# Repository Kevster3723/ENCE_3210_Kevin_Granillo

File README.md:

# ENCE_3210_Kevin_Granillo

Hello World
Kevin

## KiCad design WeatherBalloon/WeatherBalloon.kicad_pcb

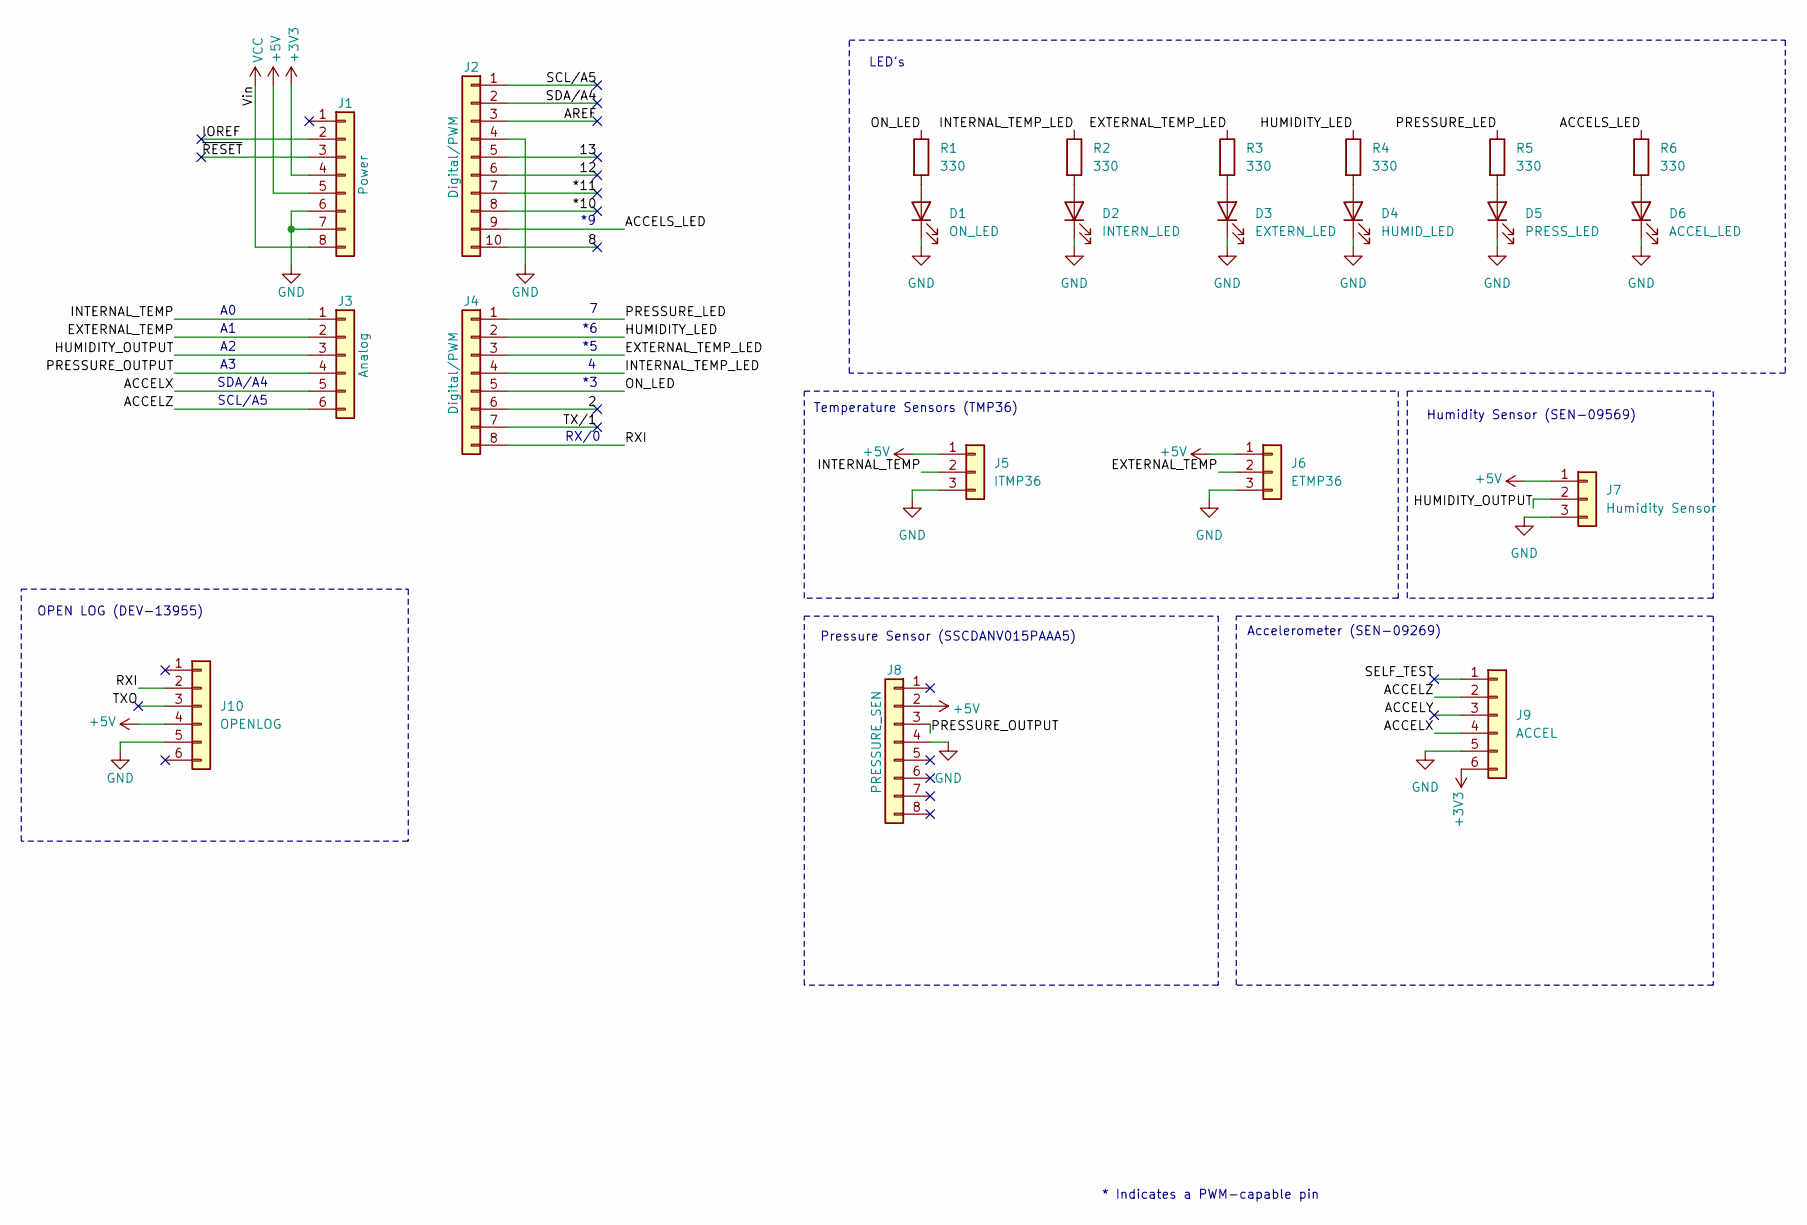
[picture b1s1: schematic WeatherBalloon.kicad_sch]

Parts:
D1: ON_LED; LED_D5.0mm
D2: INTERN_LED; LED_D5.0mm
D3: EXTERN_LED; LED_D5.0mm
D4: HUMID_LED; LED_D5.0mm
D5: PRESS_LED; LED_D5.0mm
D6: ACCEL_LED; LED_D5.0mm
J1: Power; PinSocket_1x08_P2.54mm_Vertical
J2: Digital/PWM; PinSocket_1x10_P2.54mm_Vertical
J3: Analog; PinSocket_1x06_P2.54mm_Vertical
J4: Digital/PWM; PinSocket_1x08_P2.54mm_Vertical
J5: ITMP36; TMP36
J6: ETMP36; TMP36
J7: Humidity Sensor; PinHeader_1x03_P2.54mm_Vertical
J8: PRESSURE_SEN; DIP-8_W7.62mm
J9: ACCEL; PinHeader_1x06_P2.54mm_Vertical
J10: OPENLOG; PinHeader_1x06_P2.00mm_Vertical
R1, R2, R3, R4, R5, R6: 330; R_Axial_DIN0207_L6.3mm_D2.5mm_P10.16mm_Horizontal

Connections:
+3V3: J1.4, J9.6
+5V: J1.5, J5.1, J6.1, J7.1, J8.2, J10.4
/2: J4.6
/8: J2.10
/12: J2.6
/13: J2.5
/*10: J2.8
/*11: J2.7
/ACCELS_LED: J2.9, R6.1
/ACCELX: J3.5, J9.4
/ACCELY: J9.3
/ACCELZ: J3.6, J9.2
/AREF: J2.3
/EXTERNAL_TEMP: J3.2, J6.2
/EXTERNAL_TEMP_LED: J4.3, R3.1
/HUMIDITY_LED: J4.2, R4.1
/HUMIDITY_OUTPUT: J3.3, J7.2
/INTERNAL_TEMP: J3.1, J5.2
/INTERNAL_TEMP_LED: J4.4, R2.1
/IOREF: J1.2
/ON_LED: J4.5, R1.1
/PRESSURE_LED: J4.1, R5.1
/PRESSURE_OUTPUT: J3.4, J8.3
/RXI: J4.8, J10.2
/SCL/A5: J2.1
/SDA/A4: J2.2
/SELF_TEST: J9.1
/TXO: J10.3
/TX/1: J4.7
/~RESET: J1.3
GND: D1.1 (K), D2.1 (K), D3.1 (K), D4.1 (K), D5.1 (K), D6.1 (K), J1.6, J1.7, J2.4, J5.3, J6.3, J7.3, J8.4, J9.5, J10.5
unnamed: D1.2 (A), R1.2
unnamed: D2.2 (A), R2.2
unnamed: D3.2 (A), R3.2
unnamed: D4.2 (A), R4.2
unnamed: D5.2 (A), R5.2
unnamed: D6.2 (A), R6.2
VCC: J1.8

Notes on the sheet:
Accelerometer (SEN-09269)
OPEN LOG (DEV-13955)
SCL/A5
RX/0
Pressure Sensor (SSCDANV015PAAA5)
LED's
SDA/A4
* Indicates a PWM-capable pin
Temperature Sensors (TMP36)
Humidity Sensor (SEN-09569)

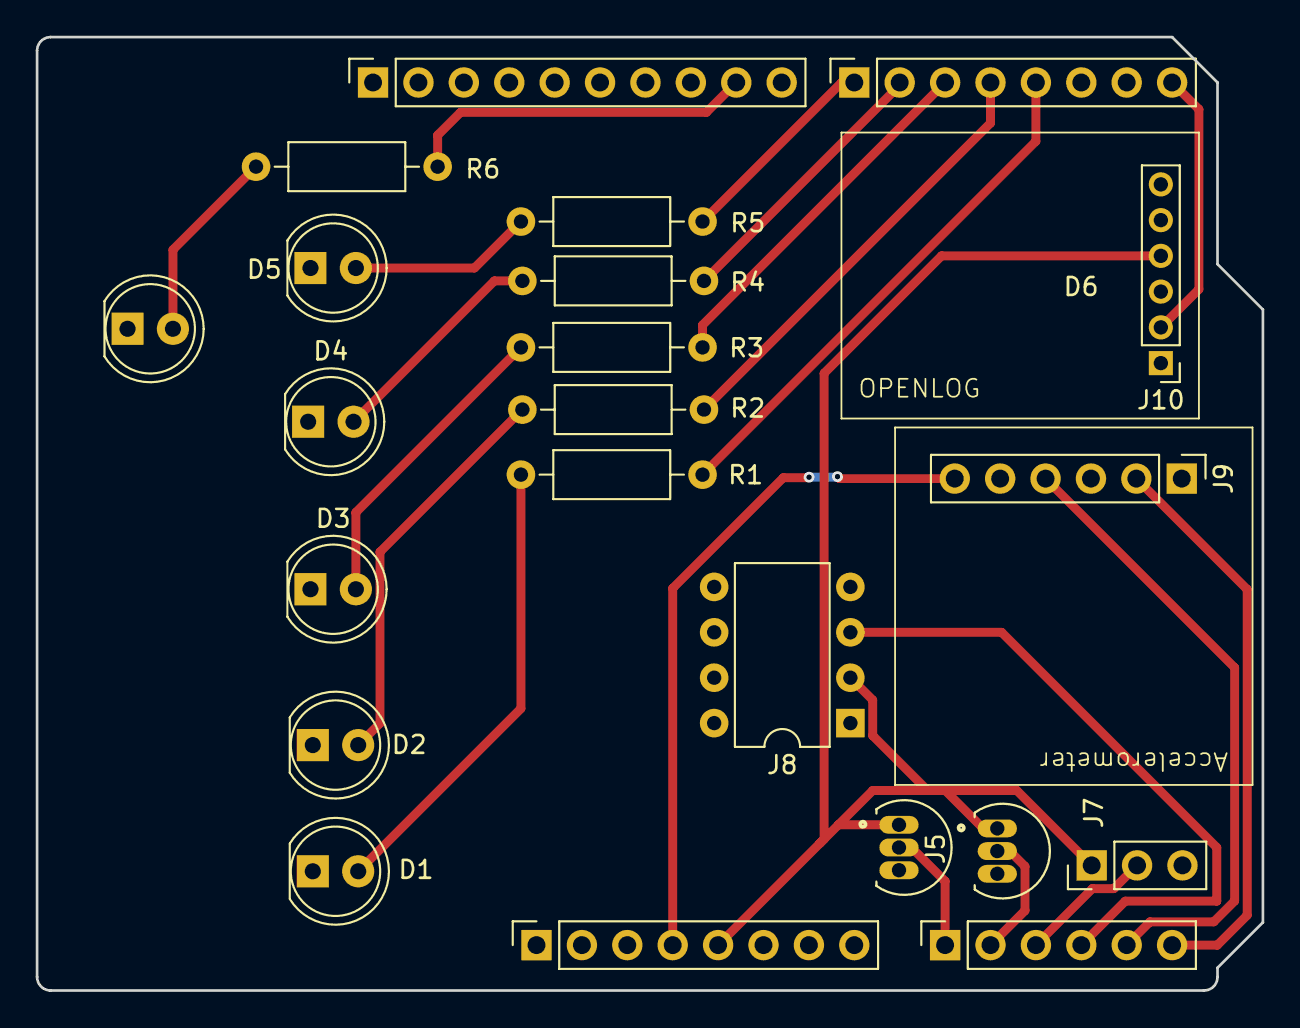
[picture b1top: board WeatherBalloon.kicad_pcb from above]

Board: 2 copper layers, 68.6 x 53.3 mm, 22 parts (0 on the bottom side), 22 nets.

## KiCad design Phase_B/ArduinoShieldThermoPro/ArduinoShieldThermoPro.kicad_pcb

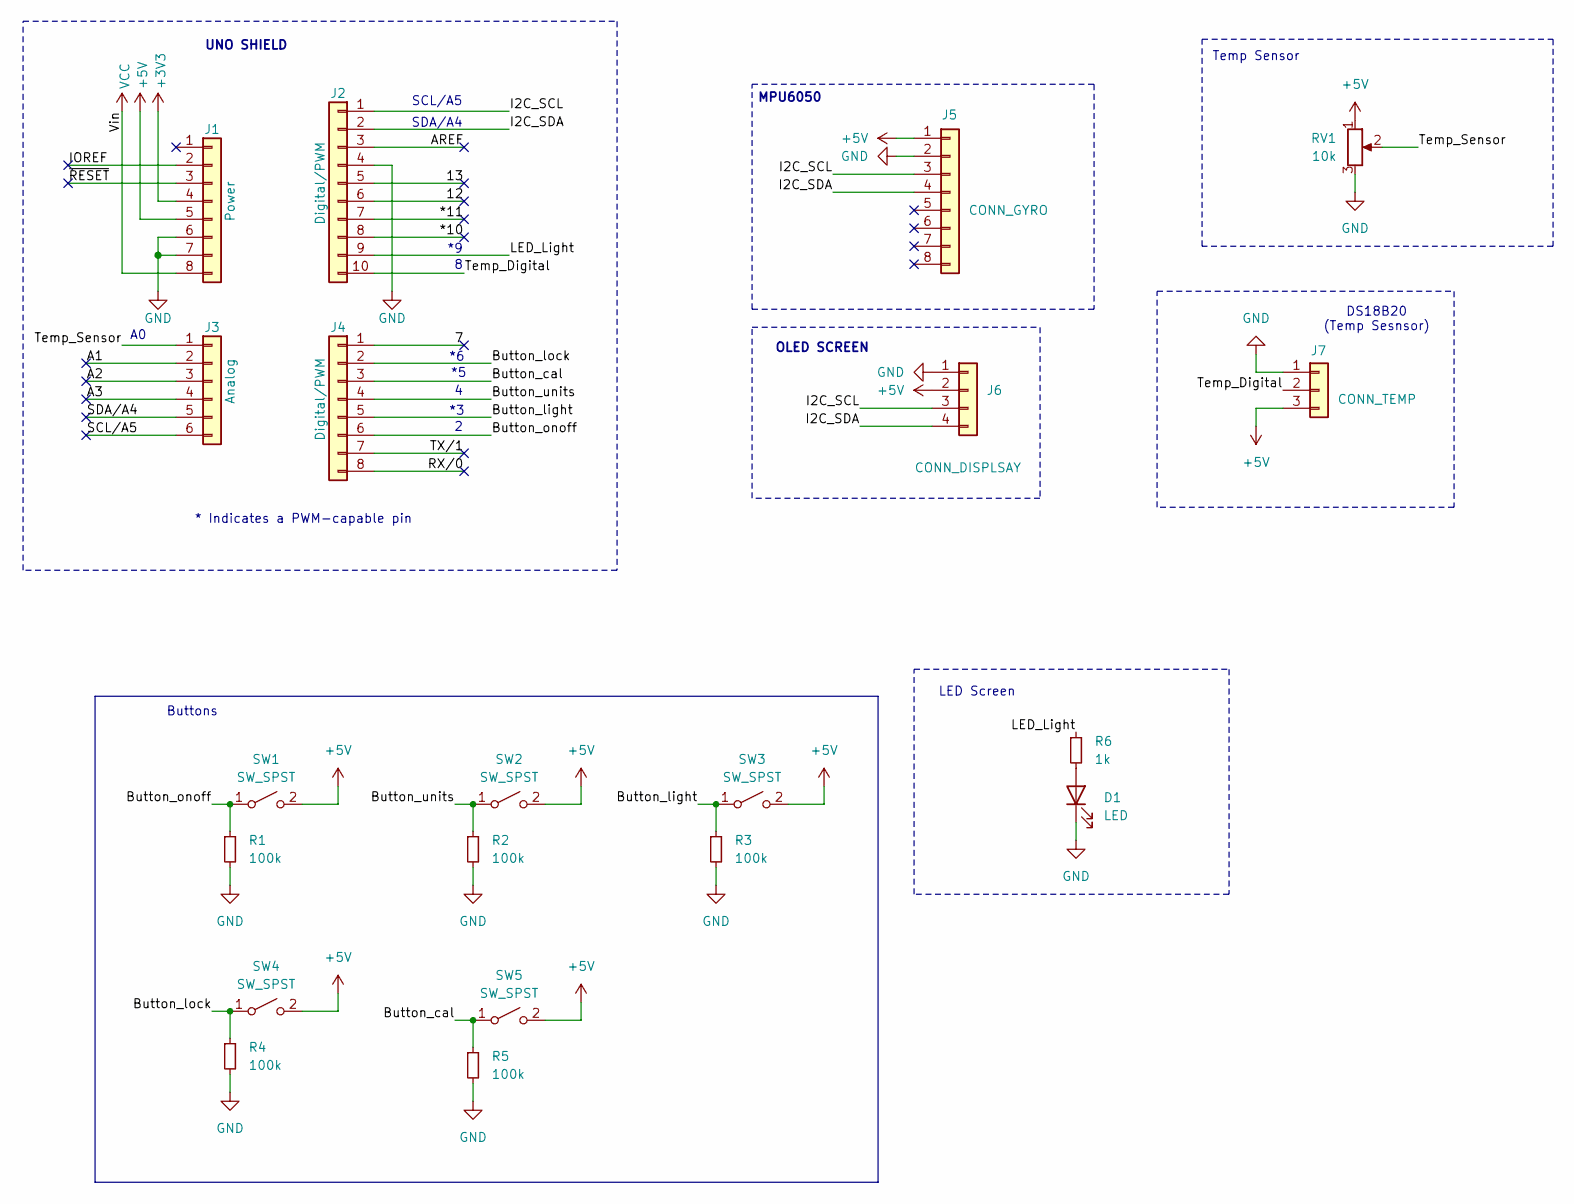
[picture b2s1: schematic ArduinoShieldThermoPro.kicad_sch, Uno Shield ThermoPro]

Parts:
D1: LED; LED_D5.0mm
J1: Power; PinSocket_1x08_P2.54mm_Vertical
J2: Digital/PWM; PinSocket_1x10_P2.54mm_Vertical
J3: Analog; PinSocket_1x06_P2.54mm_Vertical
J4: Digital/PWM; PinSocket_1x08_P2.54mm_Vertical
J5: CONN_GYRO; PinSocket_1x08_P2.54mm_Vertical
J6: CONN_DISPLSAY; PinSocket_1x04_P2.54mm_Vertical
J7: CONN_TEMP; JST_XH_B3B-XH-A_1x03_P2.50mm_Vertical
R1, R2, R3, R4, R5: 100k; R_Axial_DIN0207_L6.3mm_D2.5mm_P10.16mm_Horizontal
R6: 1k; R_Axial_DIN0207_L6.3mm_D2.5mm_P10.16mm_Horizontal
RV1: 10k; Potentiometer_Bourns_3386P_Vertical
SW1, SW2, SW3, SW4, SW5: SW_SPST; SW_PUSH_6mm

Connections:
+3V3: J1.4
+5V: J1.5, J5.1, J6.2, J7.3, RV1.1, SW1.2 (B), SW2.2 (B), SW3.2 (B), SW4.2 (B), SW5.2 (B)
/7: J4.1
/12: J2.6
/13: J2.5
/*10: J2.8
/*11: J2.7
/A1: J3.2
/A2: J3.3
/A3: J3.4
/AREF: J2.3
/Button_cal: J4.3, R5.1, SW5.1 (A)
/Button_light: J4.5, R3.1, SW3.1 (A)
/Button_lock: J4.2, R4.1, SW4.1 (A)
/Button_onoff: J4.6, R1.1, SW1.1 (A)
/Button_units: J4.4, R2.1, SW2.1 (A)
/I2C_SCL: J2.1, J5.3, J6.3
/I2C_SDA: J2.2, J5.4, J6.4
/IOREF: J1.2
/LED_Light: J2.9, R6.1
/RX/0: J4.8
/SCL/A5: J3.6
/SDA/A4: J3.5
/TX/1: J4.7
/Temp_Digital: J2.10, J7.2
/Temp_Sensor: J3.1, RV1.2
/~RESET: J1.3
GND: D1.1 (K), J1.6, J1.7, J2.4, J5.2, J6.1, J7.1, R1.2, R2.2, R3.2, R4.2, R5.2, RV1.3
unnamed: D1.2 (A), R6.2
VCC: J1.8

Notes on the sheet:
DS18B20 (Temp Sesnsor)
MPU6050
OLED SCREEN
LED Screen
Temp Sensor
Buttons
UNO SHIELD
SDA/A4
* Indicates a PWM-capable pin
SCL/A5

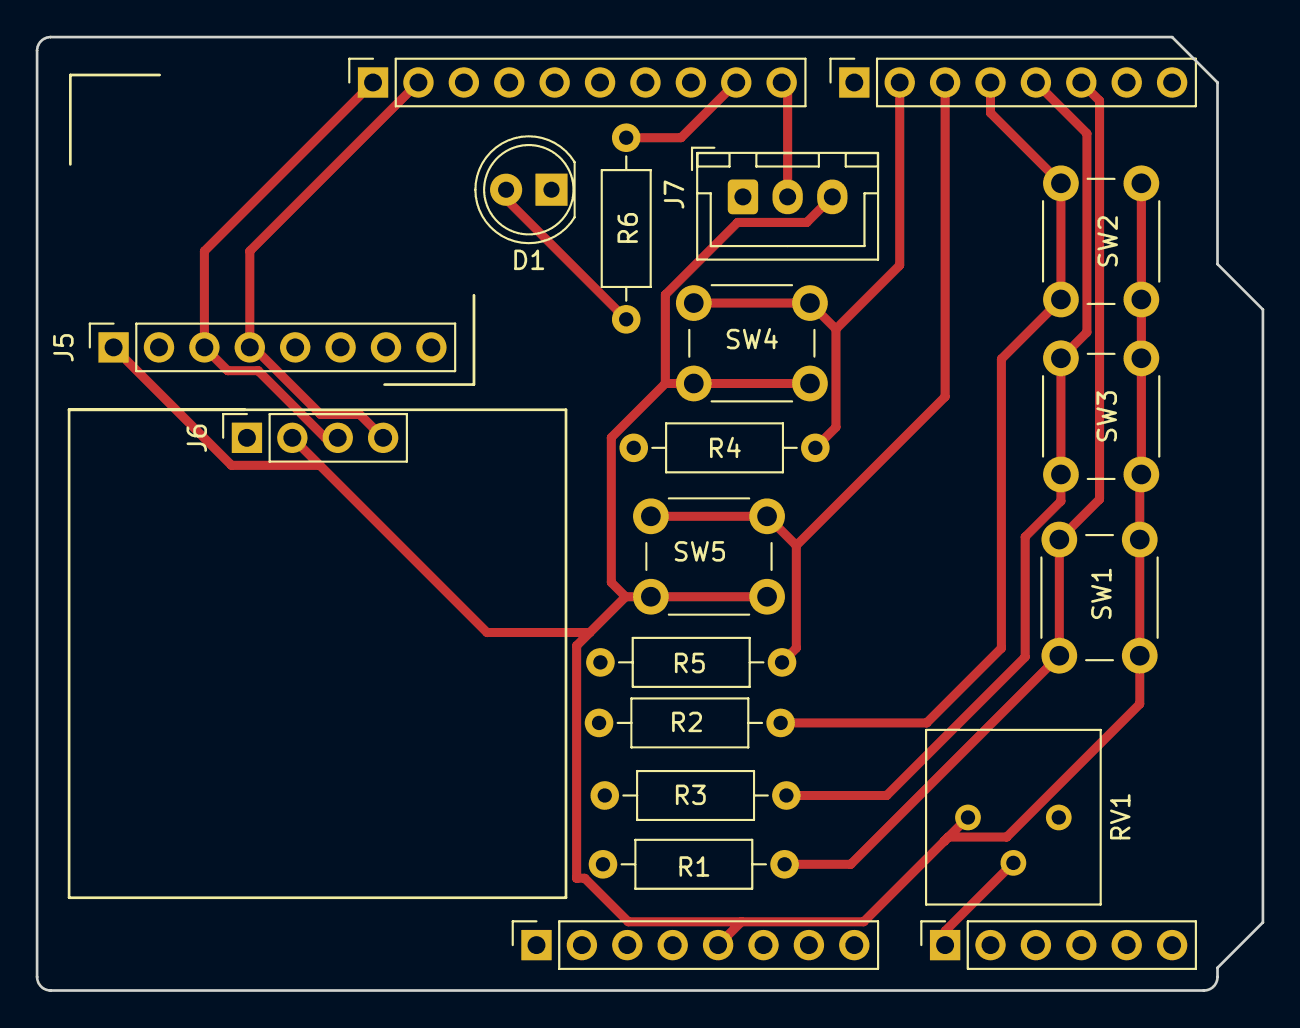
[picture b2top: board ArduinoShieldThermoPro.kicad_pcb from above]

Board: 2 copper layers, 68.6 x 53.3 mm, 20 parts (0 on the bottom side), 13 nets.

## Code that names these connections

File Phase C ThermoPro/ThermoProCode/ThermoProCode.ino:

/*
*
* Kevin Granillo
* February 26, 2025
*
* This code is made for a thermometer that uses a one wire digital temperature sensor
* The criteria for the thermometer are that it must switch between celcius and fahrenheit
* It must flip the screen orientation depending on the gyro readings
* It must have a button for the light on the back lit display
* Lastly, it must lock the reading when a button is pressed
*
* Side note, everything works well, the only issue ecnountered was with the mechanical buttons which bounce
*
*/

// Defining all buttons used
#define BUTTON_LOCK 3
#define BUTTON_CAL 5
#define BUTTON_UNITS 4
#define BUTTON_LIGHT 6
#define BUTTON_ONOFF 2

#define LED 9 // LED for backlit display

#define TEMP_DIGITAL 8 // Digital Temp Sensor
#define TEMP_ANALOG A0 // Potentiometer playing as analog Temp Sensor

#define TIMERCOMPAREVALUE1 46875 // Resets Timer 1 after 3 seconds
#define TIMERCOMPAREVALUE2 255 // Resets Timer 2 after overflow

#define ONE_WIRE_BUS 8 // Temp Sensor Pin
#define OUTPUT_READABLE_ACCELGYRO

// All included libraries for Temp sensor, gyro, and Screen
#include <SPI.h>
#include <OneWire.h>
#include <DallasTemperature.h>
#include <Adafruit_GFX.h>
#include <Adafruit_SSD1306.h>
#include <I2Cdev.h>
#include <MPU6050.h>
#include "images.h" // Images displayed on screen (LOCK, UNCLOCKED LOCK, C,F)

#define SCREEN_WIDTH 128 // OLED display width, in pixels
#define SCREEN_HEIGHT 32 // OLED display height, in pixels

#if I2CDEV_IMPLEMENTATION == I2CDEV_ARDUINO_WIRE
    #include "Wire.h"
#endif

// Declaration for an SSD1306 display connected to I2C (SDA, SCL pins)
// The pins for I2C are defined by the Wire-library. 
// On an arduino UNO:       A4(SDA), A5(SCL)
// On an arduino MEGA 2560: 20(SDA), 21(SCL)
// On an arduino LEONARDO:   2(SDA),  3(SCL), ...
#define OLED_RESET     -1 // Reset pin # (or -1 if sharing Arduino reset pin)
#define SCREEN_ADDRESS 0x3C ///< See datasheet for Address; 0x3D for 128x64, 0x3C for 128x32
Adafruit_SSD1306 display(SCREEN_WIDTH, SCREEN_HEIGHT, &Wire, OLED_RESET);

OneWire oneWire(ONE_WIRE_BUS);
DallasTemperature sensors(&oneWire);

enum State_e{OFF,ON,LOCK}; // Defines state machine (On, Off, and Locked)
enum State_e gState = OFF; // Default state is off

// Global Variables for Temp
float gTempC = 0;
float gTempF = 0;

// Global Variables used as flags
char gFlag_OnOff = 0;
char gFlag_Lock = 0;
char gFlag_Units = 0; 
char gFlag_Light = 0;
char gFlag_ReadTemp = 0;

// Variables for Gyroscope
int16_t ax, ay, az;
int16_t gx, gy, gz;
MPU6050 accelgyro;
//MPU6050 accelgyro(0x69); // <-- use for AD0 high



void setup() {
  Serial.begin(9600); // Begin Serial Comunication 

  // Buttons and Sensors are Inputs, LED is output
  pinMode(BUTTON_LOCK,INPUT);
  pinMode(BUTTON_CAL,INPUT);
  pinMode(BUTTON_UNITS,INPUT);
  pinMode(BUTTON_LIGHT,INPUT);
  pinMode(BUTTON_ONOFF,INPUT);
  pinMode(TEMP_DIGITAL,INPUT);
  pinMode(TEMP_ANALOG,INPUT);
  pinMode(LED,OUTPUT);

#if I2CDEV_IMPLEMENTATION == I2CDEV_ARDUINO_WIRE
  Wire.begin();
#elif I2CDEV_IMPLEMENTATION == I2CDEV_BUILTIN_FASTWIRE
  Fastwire::setup(400, true);
#endif

  sensors.begin();
  accelgyro.initialize();

  // SSD1306_SWITCHCAPVCC = generate display voltage from 3.3V internally
  if(!display.begin(SSD1306_SWITCHCAPVCC, SCREEN_ADDRESS)) {
    Serial.println(F("SSD1306 allocation failed"));
    for(;;); // Don't proceed, loop forever
  }
  // Show initial display buffer contents on the screen --
  // the library initializes this with an Adafruit splash screen.
  display.display();
  delay(2000); // Pause for 2 seconds
  // Clear the buffer
  display.clearDisplay();

  attachInterrupt(digitalPinToInterrupt(BUTTON_ONOFF), isr_onoff,CHANGE); // Attach interrupt to OnOff button
  attachInterrupt(digitalPinToInterrupt(BUTTON_LOCK), isr_lock, CHANGE); // Attach interrupt to Lock button

  noInterrupts(); // Disable interrupts
  TCCR1B = 0; // Timer 1
  TCCR1A = 0;

  TCCR2B = 0; // Timer 2
  TCCR2A = 0;

  TCCR2B |= (1<<WGM21); // Clock set to CTC
  TCCR2B |= (1<<CS22); //Clock 2 prescale by 1024
  TCCR2B |= (1<<CS21);
  TCCR2B |= (1<<CS20);

  OCR1A = TIMERCOMPAREVALUE1; // Reset after 3 seconds
  OCR2A = TIMERCOMPAREVALUE2; // Reset after overflow

  TIMSK1 |= (1<<OCIE1A); // Attach interrupt to timer 1
  TIMSK2 |= (1<<OCIE2A); // Attach interrupt to timer 2
  
  interrupts(); // Enable interrupts
}

void loop() {
  // put your main code here, to run repeatedly:
  display.clearDisplay(); // Clear display after each itteration 
  accelgyro.getMotion6(&ax, &ay, &az, &gx, &gy, &gz); // Read Gyro

  switch(gState){ // State Machine
  
    case OFF:
      display.clearDisplay(); // When State is off, display is off
    break;

    case ON: // When State is on, the temperature is read, units are attached and temp is displayed
      ReadTemp();
      Units();
      DisplayTemp();
    break;

    case LOCK:
      DisplayTemp(); // When Lock state, Temp no longer read just displayed with units
      Units();
    break;

  }
  OnOff(); // Checks if OnOff button has been pressed
  LockStatus(); // Checks if Lock button has been pressed
  Light(); // Checks if Light button has been pressed
  display.display(); // Updates the display
}

void OnOff()
{
  if(gFlag_OnOff) // If the button has been pressed, on off state will be toggled
  {
    gState = ON;
  } else 
  {
    gState = OFF;
  }
}

void LockStatus()
{
  if(gFlag_Lock && gFlag_OnOff) // If the Lock button has been pressed change state to Lock
  {
    gState = LOCK;
  }
}

void Units()
{
  if(digitalRead(BUTTON_UNITS)) // If Units button has been pressed initialize timer 1
  {
    TCCR1B |= (1<<WGM12);
    TCCR1B |= (1<<CS12);
    TCCR1B |= (1<<CS10);
  } else // If button is no longer pressed, stop timer 1
  {
    TCCR1B &= (0<<WGM12);
    TCCR1B &= (0<<CS12);
    TCCR1B &= (0<<CS10);
  }
}

void ReadTemp()
{
  if(gFlag_ReadTemp) // If timer 2 has reset, read temperature
  {
    sensors.requestTemperatures();
  }
  gTempC = sensors.getTempCByIndex(0); // Temperature in Celsius 
  gTempF = sensors.getTempFByIndex(0); // Temperature in Fahrenheit
}

void DisplayTemp()
{
    display.clearDisplay();
    display.setTextSize(2);      // Normal 2:2 pixel scale
    display.setTextColor(SSD1306_WHITE); // Draw white text
    display.setCursor(0, 10);     // Start on left side halfway down
    display.cp437(true);  
  if(gFlag_Units)
  {
    display.print(gTempF); // Display Temp in Fahrenheit
    display.drawBitmap(0,0, images[3],SCREEN_WIDTH,SCREEN_HEIGHT,WHITE); // If Temp is in Fahrenheit, Display "F" after temp
  } else 
  {
    display.print(gTempC); // Display Temp in Celcius
    display.drawBitmap(0,0, images[2],SCREEN_WIDTH,SCREEN_HEIGHT,WHITE); // If Temp is in Fahrenheit, Display "F" after temp
  }
  if(gState == ON)
  {
    display.drawBitmap(0,0, images[1],SCREEN_WIDTH,SCREEN_HEIGHT,WHITE); // If not Locked, display open lock
  } else if(gState == LOCK)
  {
    display.drawBitmap(0,0, images[0],SCREEN_WIDTH,SCREEN_HEIGHT,WHITE); // If locked, display closed lock
  }
#ifdef OUTPUT_READABLE_ACCELGYRO
  // Read x acceleration and orient screen accordingly
    if (ax < 0){ 
      display.setRotation(2); // Flips screen 180 degrees
    }
    else{
      display.setRotation(0); // Shows default screen orientation
    }
  #endif
}

void Light()
{
  if(digitalRead(BUTTON_LIGHT) && gState != OFF) // If button light is pressed and the screen is not off
  {
    gFlag_Light = !gFlag_Light; // Toggle flag
  }
  if(gFlag_Light) // If true, turn on LED else turn off
  {
    digitalWrite(LED,HIGH);
  } else
  {
    digitalWrite(LED,LOW);
  } 
}


void isr_onoff() // Interrupt service routine for OnOff button
{
  if(digitalRead(BUTTON_ONOFF)) // If on off button pressed, toggle flag to turn screen on or off
  {
    gFlag_OnOff = !gFlag_OnOff;
  }
}

void isr_lock() // Interrupt Service Routine for Lock button
{
  if(digitalRead(BUTTON_LOCK) && gState != OFF) // If button is pressed toggle flag to lock and unlock
  {
    gFlag_Lock = !gFlag_Lock;
  }
}

ISR(TIMER1_COMPA_vect) // Interrupt service routine for Timer 1
{
  gFlag_Units = !gFlag_Units; // Flag is toggled after 3 seconds
}

ISR(TIMER2_COMPA_vect) // Interrupt service routine for Timer 2
{
  gFlag_ReadTemp = !gFlag_ReadTemp; // After timer 2 overflow toggle flag to read Temp
}

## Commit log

2025-01-10 lab 1 Pt 3
2025-01-17 Lab 1
2025-01-17 Updated Problem 6
2025-01-24 Lab 2
2025-01-31 Phase B
2025-01-31 Lab 3
2025-02-03 Update to PCB
2025-02-03 Update PCB
2025-02-03 Added pdf of Schematic
2025-02-03 Added BOM
2025-02-04 Added docs and gerber files
2025-02-04 Added Board diagram
2025-02-12 Updating PCB
2025-02-26 Phase C ThermoPro
2025-03-01 Lab 4
2025-03-14 Weather Balloon
2025-03-14 Update DS Store
2025-03-14 Added Presentation
